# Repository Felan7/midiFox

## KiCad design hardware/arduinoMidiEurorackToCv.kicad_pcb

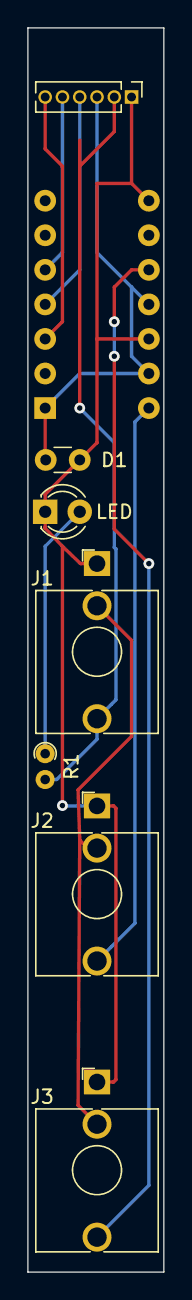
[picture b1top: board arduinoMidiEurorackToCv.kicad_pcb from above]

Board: 2 copper layers, 10.0 x 91.4 mm, 8 parts (1 on the bottom side), 9 nets.

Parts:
D1: LED; LED_D3.0mm
J1: Gate Out; Jack_3.5mm_QingPu_WQP-PJ398SM_Vertical_CircularHoles
J2: NoteOut; Jack_3.5mm_QingPu_WQP-PJ398SM_Vertical_CircularHoles
J3: VelocityOut; Jack_3.5mm_QingPu_WQP-PJ398SM_Vertical_CircularHoles
J5: Con; PinHeader_1x06_P1.27mm_Vertical
LED: C; C_Disc_D3.0mm_W1.6mm_P2.50mm
MCP 4922: MCP4922; DIP-14_W7.62mm_Socket
R1: R_Small; R_Axial_DIN0204_L3.6mm_D1.6mm_P1.90mm_Vertical

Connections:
5V: J5.3, LED.2, MCP 4922.1, MCP 4922.11, MCP 4922.13
GND: D1.1, J1.S, J2.S, J3.S, J5.1, LED.1, MCP 4922.8, MCP 4922.12
unnamed: D1.2, R1.1
unnamed: J1.T, J5.2, R1.2
unnamed: J2.T, MCP 4922.14
unnamed: J3.T, MCP 4922.10
unnamed: J5.4, MCP 4922.4
unnamed: J5.5, MCP 4922.5
unnamed: J5.6, MCP 4922.3

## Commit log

2020-12-04 Inital Commit
2020-12-13 Added schematic files
2021-01-13 Added Manual
